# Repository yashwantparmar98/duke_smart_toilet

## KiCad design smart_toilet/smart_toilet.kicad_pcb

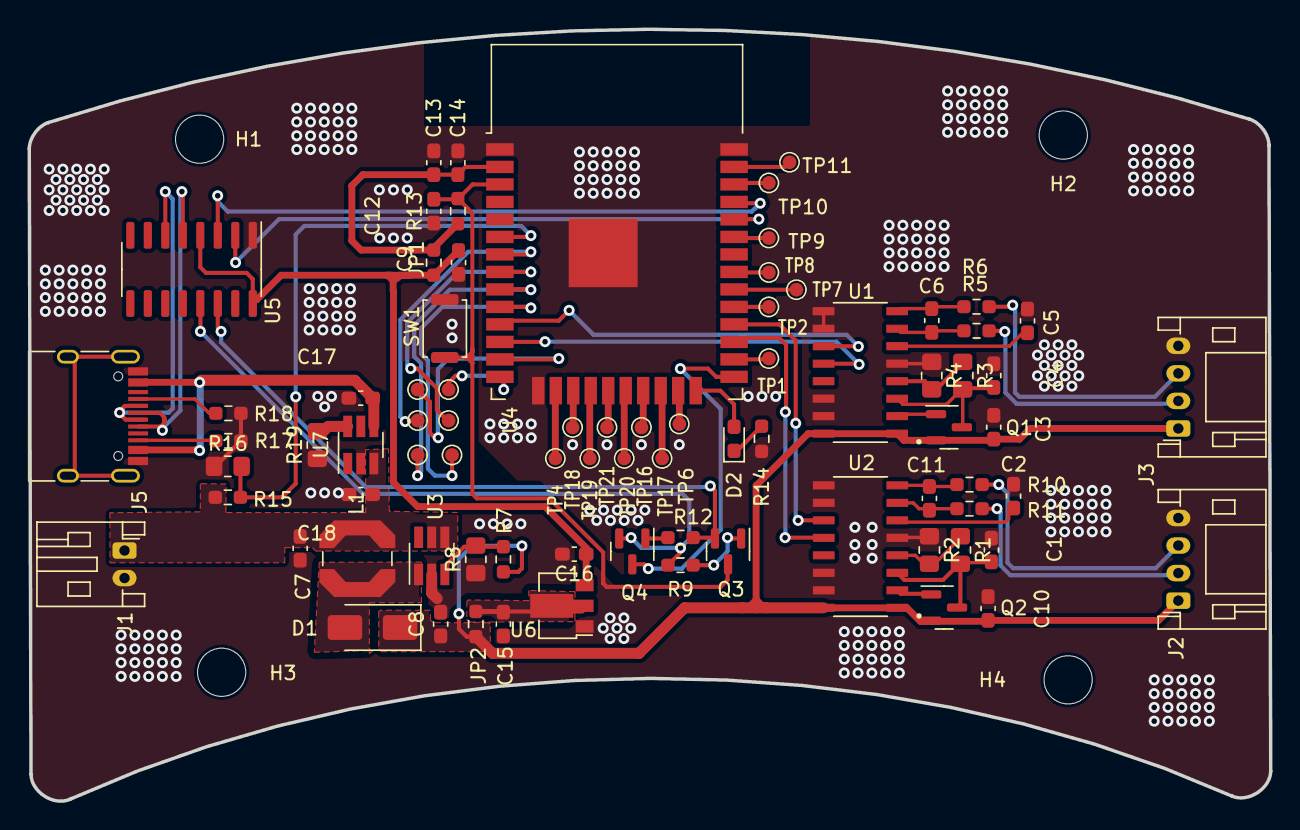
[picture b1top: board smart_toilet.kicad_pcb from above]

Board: 2 copper layers, 90.1 x 56.0 mm, 83 parts (0 on the bottom side), 66 nets.

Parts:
C1, C3, C4, C10, C17, C18: 10uF; C_0603_1608Metric_Pad1.08x0.95mm_HandSolder
C2, C5, C6, C11: 0.1uF; C_0603_1608Metric_Pad1.08x0.95mm_HandSolder
C7, C8, C14, C15, C16: 22uF; C_0603_1608Metric_Pad1.08x0.95mm_HandSolder
C9, C12, C13: 100nF; C_0603_1608Metric_Pad1.08x0.95mm_HandSolder
D1: SS34; D_SMA
D2: LED; LED_0603_1608Metric_Pad1.05x0.95mm_HandSolder
H1, H2, H3, H4: MountingHole; MountingHole_3.5mm
J1: Conn_01x02; JST_PH_S2B-PH-K_1x02_P2.00mm_Horizontal
J2, J3: Conn_01x04; JST_PH_S4B-PH-K_1x04_P2.00mm_Horizontal
J5: USB_C_Receptacle_USB2.0; USB_C_Receptacle_HRO_TYPE-C-31-M-12
JP1, JP2: jumper; R_0603_1608Metric_Pad0.98x0.95mm_HandSolder
L1: 4.7uH; L_Coilcraft_LPS5030
Q1, Q2: BC860; SOT-23
Q3, Q4: MMBT5550L; SOT-23
R1, R3, R8: 20K; R_0805_2012Metric_Pad1.20x1.40mm_HandSolder
R2, R4: 8.2K; R_0805_2012Metric_Pad1.20x1.40mm_HandSolder
R5, R6, R10, R11: 1.2K; R_0603_1608Metric_Pad0.98x0.95mm_HandSolder
R7: 150K; R_0603_1608Metric_Pad0.98x0.95mm_HandSolder
R9, R12, R13, R14: 10K; R_0603_1608Metric_Pad0.98x0.95mm_HandSolder
R15: 500K; R_0603_1608Metric_Pad0.98x0.95mm_HandSolder
R16: 250K; R_0805_2012Metric_Pad1.20x1.40mm_HandSolder
R17, R18: 5.1K; R_0603_1608Metric_Pad0.98x0.95mm_HandSolder
R19: 1.6K; R_0805_2012Metric_Pad1.20x1.40mm_HandSolder
SW1: SW_Omron_B3FS; SW_Push_SPST_NO_Alps_SKRK
TP1, TP2, TP3, TP4, TP5, TP6, TP7, TP8, TP9, TP10, TP11, TP12, TP13, TP14, TP15, TP16, TP17, TP18, TP19, TP20, TP21: TestPoint; TestPoint_Pad_D1.0mm
U1, U2: HX711; SOP127P600X180-16N
U3: SX1308; SOT-23-6_Handsoldering
U4: ESP32-WROOM-32D; ESP32-WROOM-32
U5: CH340C; SOIC-16_3.9x9.9mm_P1.27mm
U6: HT7833-1-SOT89; SOT-89-3
U7: TP4057; SOT-23-6_Handsoldering

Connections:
+3.3V: C9.1, C16.1, JP1.1 (A), U5.4 (V3), U5.16 (VCC), U6.3 (VOUT)
+5V: C3.1, C8.1, C10.1, D1.1 (K), J2.1, J3.1, JP2.1 (A), Q1.2 (E), Q2.2 (E), R7.2, U1.1 (VSUP), U1.16 (DVDD), U2.1 (VSUP), U2.16 (DVDD)
+BATT: C7.1, C18.2, J1.1, L1.1, R15.2, U3.4 (EN), U3.5 (IN), U7.3 (BAT)
/E+: C4.1, Q1.3 (C), R3.2, U1.3 (AVDD)
/E+_1: C1.1, Q2.3 (C), R1.2, U2.3 (AVDD)
/SW: D1.2 (A), L1.2, U3.1 (SW)
BTSENS: R15.1, R16.2, U4.6 (IO34)
DN: J5.A7 (D-), J5.B7 (D-), U5.6 (UD-)
DOUT1: U1.12 (DOUT), U4.12 (IO27)
DOUT2: U2.12 (DOUT), U4.27 (IO16)
DP: J5.A6 (D+), J5.B6 (D+), U5.5 (UD+)
DTR: Q4.2 (E), R9.2, U5.13 (~DTR)
ESP_EN: C12.1, Q3.3 (C), R13.1, SW1.2, U4.3 (EN)
GND: C1.2, C2.2, C3.2, C4.2, C5.2, C7.2, C8.2, C9.2, C10.2, C12.2, C13.2, C14.2, C15.2, C16.2, C17.1, C18.1, J1.2, J2.4, J3.4, J5.A1 (GND), J5.A12 (GND), J5.B1 (GND), J5.B12 (GND), R2.1, R4.1, R8.1, R14.1, R16.1, R17.1, R18.1, R19.1, SW1.1, U1.5 (AGND), U1.9 (INPB), U1.10 (INNB), U1.14 (XI), U1.15 (RATE), U2.5 (AGND), U2.9 (INPB), U2.10 (INNB), U2.14 (XI), U2.15 (RATE), U3.2 (GND), U4.1 (GND), U4.15 (GND), U4.38 (GND), U4.39 (GND), U5.1 (GND), U6.1 (GND), U7.2 (GND)
IO0: Q4.3 (C), U4.25 (IO0)
IO2: D2.2 (A), U4.24 (IO2)
unnamed: D2.1 (K), R14.2
unnamed: J5.A5 (CC1), R18.2
unnamed: J5.B5 (CC2), R17.2
unnamed: C15.1, JP2.2 (B), U6.2 (VIN)
unnamed: Q1.1 (B), U1.2 (BASE)
unnamed: Q2.1 (B), U2.2 (BASE)
unnamed: Q3.1 (B), R9.1
unnamed: Q4.1 (B), R12.1
unnamed: C6.1, R5.2, U1.7 (INNA)
unnamed: C6.2, R6.1, U1.8 (INPA)
unnamed: C5.1, U1.6 (VBG)
unnamed: R3.1, R4.2, U1.4 (VFB)
unnamed: C11.1, R11.2, U2.7 (INNA)
unnamed: C11.2, R10.1, U2.8 (INPA)
unnamed: C2.1, U2.6 (VBG)
unnamed: R1.1, R2.2, U2.4 (VFB)
unnamed: R7.1, R8.2, U3.3 (FB)
unnamed: TP1.1, U4.26 (IO4)
unnamed: TP2.1, U4.29 (IO5)
unnamed: TP3.1, U4.14 (IO12)
unnamed: TP4.1, U4.16 (IO13)
unnamed: TP5.1, U4.13 (IO14)
unnamed: TP6.1, U4.23 (IO15)
unnamed: TP7.1, U4.30 (IO18)
unnamed: TP8.1, U4.31 (IO19)
unnamed: TP9.1, U4.33 (IO21)
unnamed: TP10.1, U4.36 (IO22)
unnamed: TP11.1, U4.37 (IO23)
unnamed: TP12.1, U4.10 (IO25)
unnamed: TP13.1, U4.8 (IO32)
unnamed: TP14.1, U4.9 (IO33)
unnamed: TP15.1, U4.7 (IO35)
unnamed: TP20.1, U4.20 (SCK/CLK)
unnamed: TP21.1, U4.19 (SCS/CMD)
unnamed: TP17.1, U4.22 (SDI/SD1)
unnamed: TP16.1, U4.21 (SDO/SD0)
unnamed: TP18.1, U4.17 (SHD/SD2)
unnamed: TP19.1, U4.18 (SWP/SD3)
unnamed: R19.2, U7.6 (PROG)
RTS: Q3.2 (E), R12.2, U5.14 (~RTS)
RX0: U4.34 (RXD0/IO3), U5.2 (TXD)
S+: J3.3, R6.2
S+_1: J2.3, R10.2
S-: J3.2, R5.1
S-_1: J2.2, R11.1
SCK1: U1.11 (PD_SCK), U4.11 (IO26)
SCK2: U2.11 (PD_SCK), U4.28 (IO17)
TX0: U4.35 (TXD0/IO1), U5.3 (RXD)
VBUS: C17.2, J5.A4 (VBUS), J5.A9 (VBUS), J5.B4 (VBUS), J5.B9 (VBUS), U7.4 (VCC)
VCC: C13.1, C14.1, JP1.2 (B), R13.2, U4.2 (VDD)

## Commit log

2023-04-12 UPDATED PCB
